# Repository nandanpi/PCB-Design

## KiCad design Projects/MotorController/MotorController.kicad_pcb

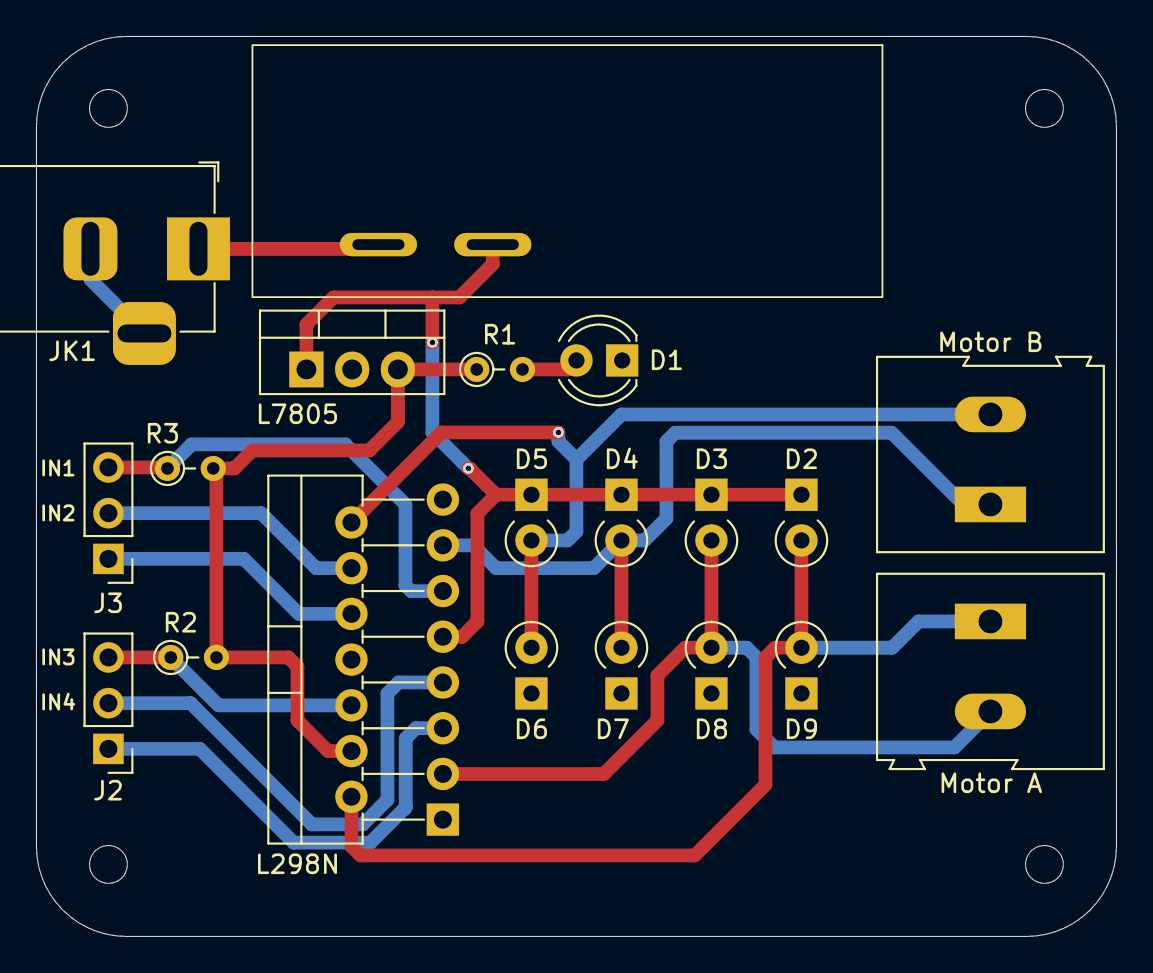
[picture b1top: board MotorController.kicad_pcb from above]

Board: 2 copper layers, 60.0 x 50.0 mm, 20 parts (0 on the bottom side), 15 nets.

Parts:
D1: LED; LED_D4.0mm
D2, D3, D4, D5, D6, D7, D8, D9: D; D_A-405_P2.54mm_Vertical_KathodeUp
J2, J3: Conn_01x03_Pin; PinHeader_1x03_P2.54mm_Vertical
JK1: BarrelJack_Horizontal
L298N: L298N; TO-220-15_P2.54x2.54mm_StaggerOdd_Lead4.58mm_Vertical
L7805: L7805; TO-220-3_Vertical
Motor A: Screw_Terminal_01x02; TerminalBlock_Altech_AK300-2_P5.00mm
Motor B: Screw_Terminal_01x02; TerminalBlock_Altech_AK300-2_P5.00mm
R1, R2, R3: R; R_Axial_DIN0204_L3.6mm_D1.6mm_P2.54mm_Vertical
SW1: SW_SPST; Slide_Switch_2pin

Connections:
+5V: L298N.4 (Vs), L7805.3 (OUT), R1.1, R2.2, R3.2
+12V: D2.1 (K), D3.1 (K), D4.1 (K), D5.1 (K), L298N.9 (Vss), L7805.1 (IN), SW1.2 (B)
GND: D1.1 (K), D6.1 (K), D7.1 (K), D8.1 (K), D9.1 (K), JK1.2 (GND), JK1.3 (MP), L298N.1 (SENSE_A), L298N.8 (GND), L298N.15 (SENSE_B), L7805.2 (GND)
unnamed: D1.2 (A), R1.2
unnamed: J2.1, L298N.5 (IN1)
unnamed: J2.2, L298N.7 (IN2)
unnamed: J2.3, L298N.6 (EnA), R2.1
unnamed: J3.1, L298N.10 (IN3)
unnamed: J3.2, L298N.12 (IN4)
unnamed: J3.3, L298N.11 (EnB), R3.1
unnamed: JK1.1 (IN), SW1.1 (A)
OUTA1: D2.2 (A), D9.2 (A), L298N.2 (OUT1), Motor A.1
OUTA2: D3.2 (A), D8.2 (A), L298N.3 (OUT2), Motor A.2
OUTB1: D4.2 (A), D7.2 (A), L298N.13 (OUT3), Motor B.1
OUTB2: D5.2 (A), D6.2 (A), L298N.14 (OUT4), Motor B.2

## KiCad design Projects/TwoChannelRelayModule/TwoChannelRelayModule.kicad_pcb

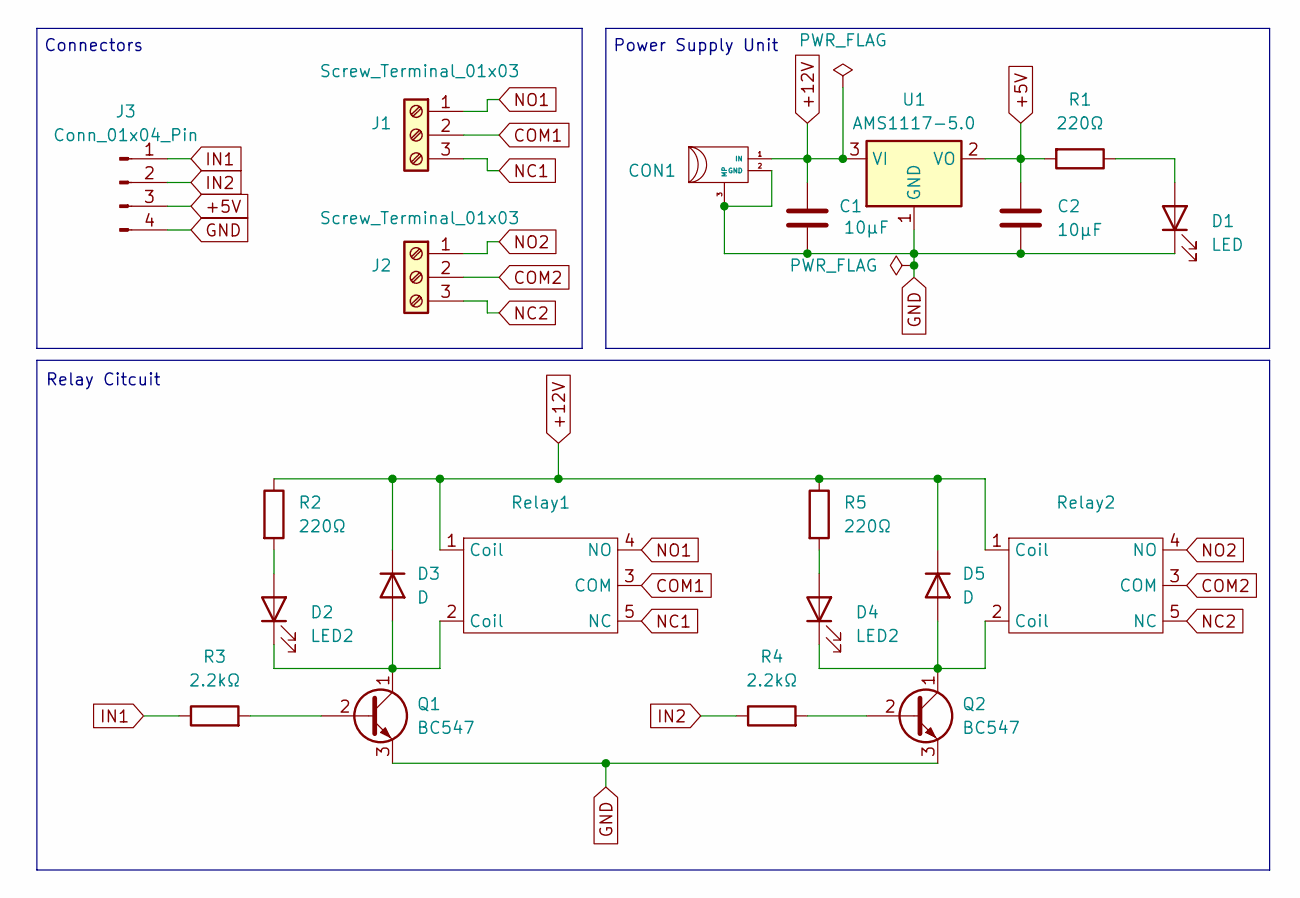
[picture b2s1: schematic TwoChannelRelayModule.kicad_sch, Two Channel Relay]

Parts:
C1, C2: 10µF; CP_Elec_4x5.8
CON1: BarrelJack_Horizontal
D1: LED; LED_0603_1608Metric
D2, D4: LED2; LED_0603_1608Metric
D3, D5: D; D_0603_1608Metric
J1, J2: Screw_Terminal_01x03; TerminalBlock_Altech_AK300-3_P5.00mm
J3: Conn_01x04_Pin; PinHeader_1x04_P2.54mm_Vertical
Q1, Q2: BC547; SOT-23
R1, R2, R5: 220Ω; R_0603_1608Metric
R3, R4: 2.2kΩ; R_0603_1608Metric
Relay1, Relay2: Relay
U1: AMS1117-5.0; SOT-223-3_TabPin2

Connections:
+5V: C2.1, J3.3, R1.2, U1.2 (VO)
+12V: C1.1, CON1.1 (IN), D3.1 (K), D5.1 (K), R2.1, R5.1, Relay1.1 (Coil), Relay2.1 (Coil), U1.3 (VI)
COM1: J1.2, Relay1.3 (COM)
COM2: J2.2, Relay2.3 (COM)
GND: C1.2, C2.2, CON1.2 (GND), CON1.3 (MP), D1.1 (K), J3.4, Q1.3 (E), Q2.3 (E), U1.1 (GND)
IN1: J3.1, R3.1
IN2: J3.2, R4.1
NC1: J1.3, Relay1.5 (NC)
NC2: J2.3, Relay2.5 (NC)
NO1: J1.1, Relay1.4 (NO)
NO2: J2.1, Relay2.4 (NO)
unnamed: D1.2 (A), R1.1
unnamed: D2.2 (A), R2.2
unnamed: D2.1 (K), D3.2 (A), Q1.1 (C), Relay1.2 (Coil)
unnamed: D4.2 (A), R5.2
unnamed: D4.1 (K), D5.2 (A), Q2.1 (C), Relay2.2 (Coil)
unnamed: Q1.2 (B), R3.2
unnamed: Q2.2 (B), R4.2

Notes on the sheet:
Relay Citcuit
Connectors
Power Supply Unit

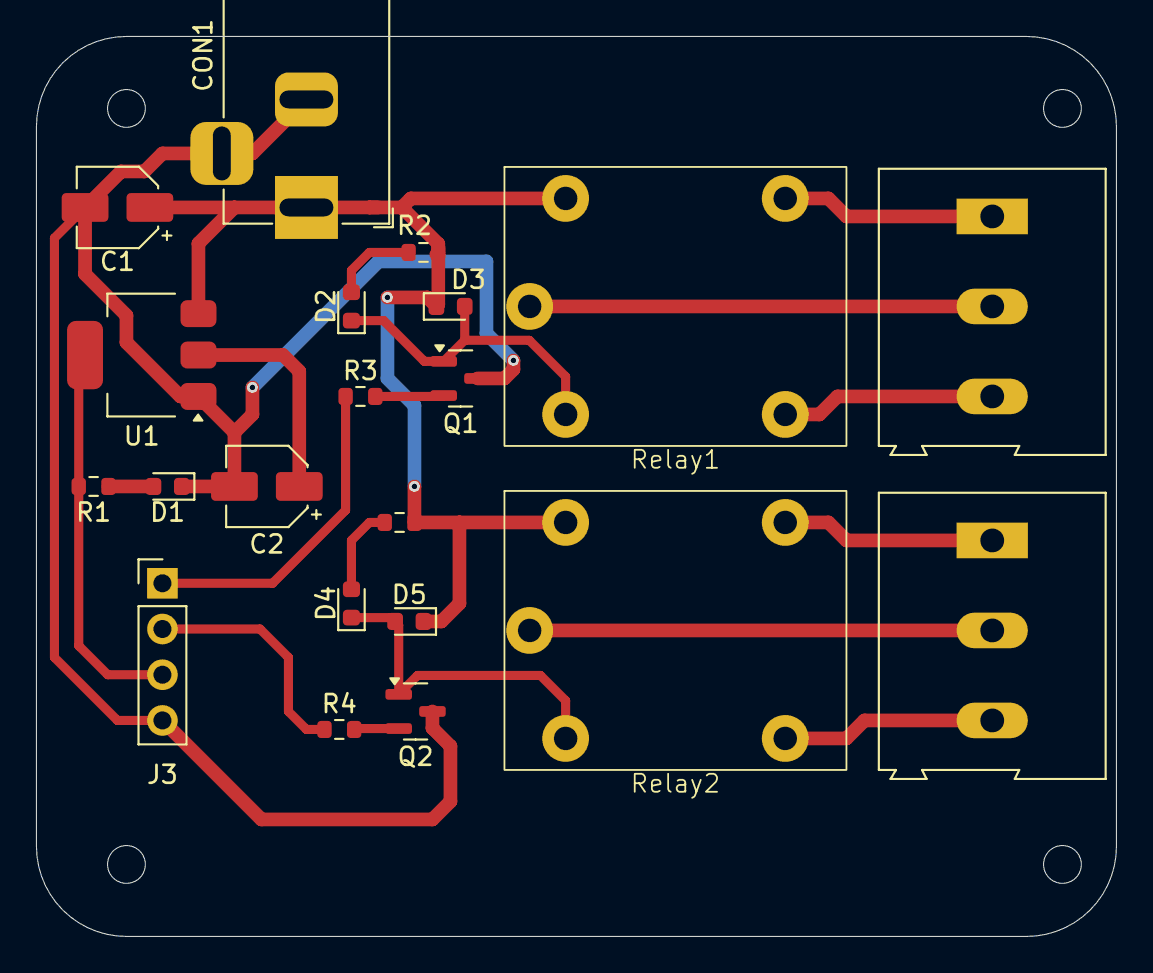
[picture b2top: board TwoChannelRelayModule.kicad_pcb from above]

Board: 2 copper layers, 60.0 x 50.0 mm, 21 parts (0 on the bottom side), 18 nets.

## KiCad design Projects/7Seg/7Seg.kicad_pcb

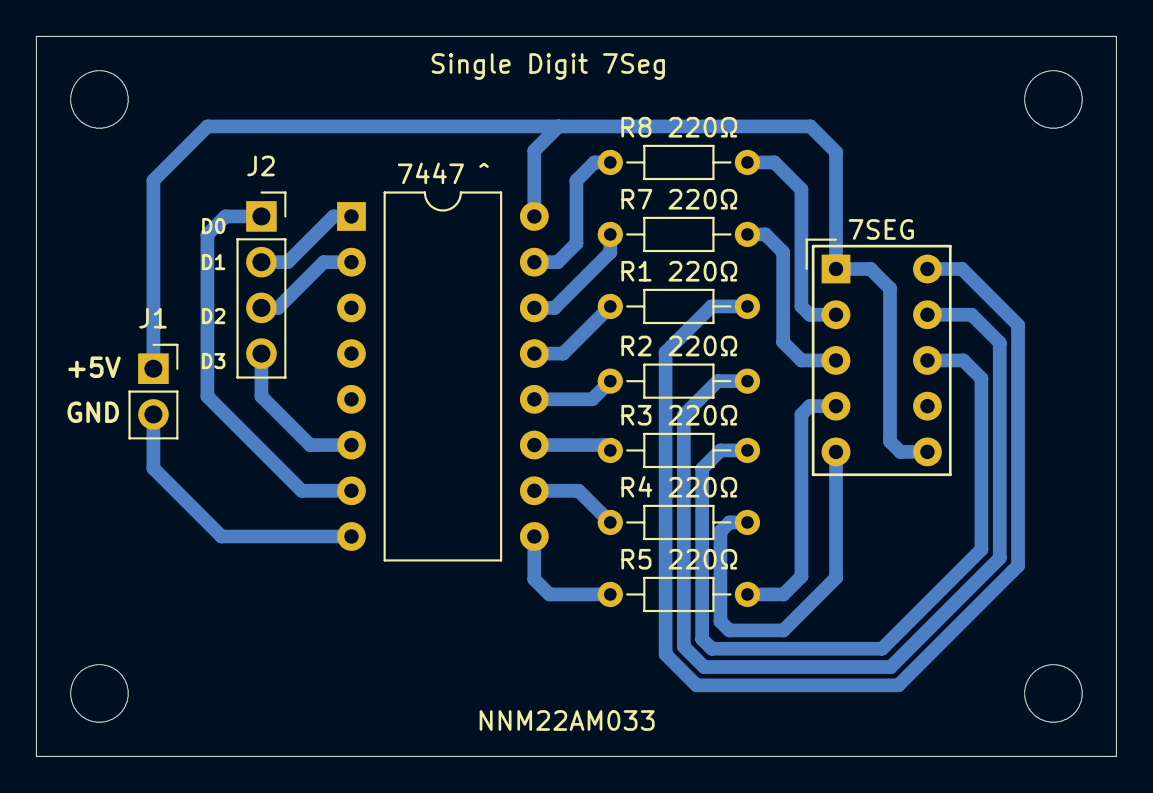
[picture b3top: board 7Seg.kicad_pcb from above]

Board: 2 copper layers, 60.0 x 40.0 mm, 11 parts (0 on the bottom side), 20 nets.

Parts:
7SEG: SA39-12EWA; HDSP-7401
7447 ^: 7447; DIP-16_W10.16mm
J1: Conn_01x02_Pin; PinSocket_1x02_P2.54mm_Vertical
J2: Conn_01x04_Pin; PinSocket_1x04_P2.54mm_Vertical
R1 220Ω, R2 220Ω, R3 220Ω, R4 220Ω, R5 220Ω, R7 220Ω, R8 220Ω: 220Ω; R_Axial_DIN0204_L3.6mm_D1.6mm_P7.62mm_Horizontal

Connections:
GND: 7447 ^.8 (GND), J1.2
unnamed: 7447 ^.7 (A), J2.1
unnamed: 7447 ^.1 (B), J2.2
unnamed: 7447 ^.2 (C), J2.3
unnamed: 7447 ^.6 (D), J2.4
unnamed: 7447 ^.13 (~a), R1 220Ω.1
unnamed: 7447 ^.12 (~b), R2 220Ω.1
unnamed: 7447 ^.11 (~c), R3 220Ω.1
unnamed: 7447 ^.10 (~d), R4 220Ω.1
unnamed: 7447 ^.9 (~e), R5 220Ω.1
unnamed: 7447 ^.15 (~f), R8 220Ω.1
unnamed: 7447 ^.14 (~g), R7 220Ω.1
unnamed: 7SEG.10 (A), R1 220Ω.2
unnamed: 7SEG.9 (B), R2 220Ω.2
unnamed: 7SEG.8 (C), R3 220Ω.2
unnamed: 7SEG.5 (D), R4 220Ω.2
unnamed: 7SEG.4 (E), R5 220Ω.2
unnamed: 7SEG.2 (F), R8 220Ω.2
unnamed: 7SEG.3 (G), R7 220Ω.2
VCC: 7SEG.1 (CA), 7SEG.6 (CA), 7447 ^.16 (VCC), J1.1

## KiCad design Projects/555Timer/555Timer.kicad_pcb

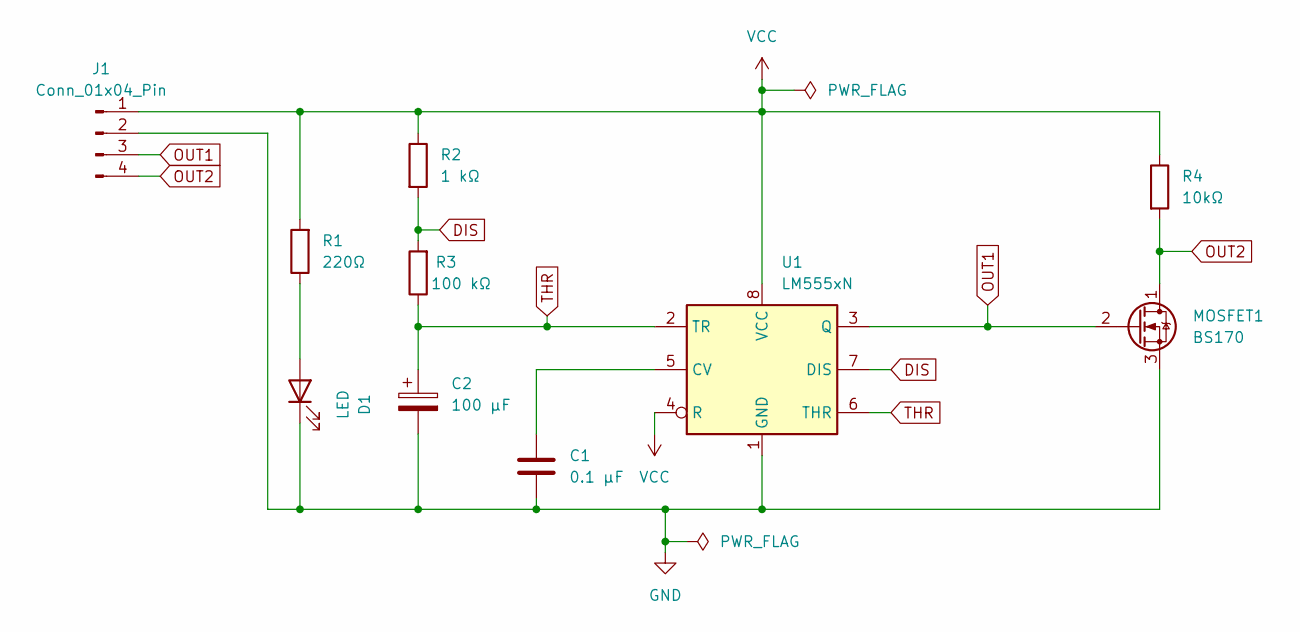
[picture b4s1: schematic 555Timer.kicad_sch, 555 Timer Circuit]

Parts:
C1: 0.1 µF; C_Disc_D5.0mm_W2.5mm_P5.00mm
C2: 100 µF; CP_Radial_Tantal_D5.0mm_P2.50mm
D1: LED; LED_D3.0mm
J1: Conn_01x04_Pin; PinSocket_1x04_P2.54mm_Vertical
MOSFET1: BS170; TO-92_Inline
R1: 220Ω; R_Axial_DIN0204_L3.6mm_D1.6mm_P7.62mm_Horizontal
R2: 1 kΩ; R_Axial_DIN0204_L3.6mm_D1.6mm_P7.62mm_Horizontal
R3: 100 kΩ; R_Axial_DIN0204_L3.6mm_D1.6mm_P7.62mm_Horizontal
R4: 10kΩ; R_Axial_DIN0204_L3.6mm_D1.6mm_P7.62mm_Horizontal
U1: LM555xN; DIP-8_W7.62mm

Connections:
DIS: R2.2, R3.2, U1.7 (DIS)
GND: C1.1, C2.2, D1.1 (K), J1.2, MOSFET1.3 (S), U1.1 (GND)
unnamed: D1.2 (A), R1.1
unnamed: C1.2, U1.5 (CV)
OUT1: J1.3, MOSFET1.2 (G), U1.3 (Q)
OUT2: J1.4, MOSFET1.1 (D), R4.2
THR: C2.1, R3.1, U1.2 (TR), U1.6 (THR)
VCC: J1.1, R1.2, R2.1, R4.1, U1.4 (R), U1.8 (VCC)

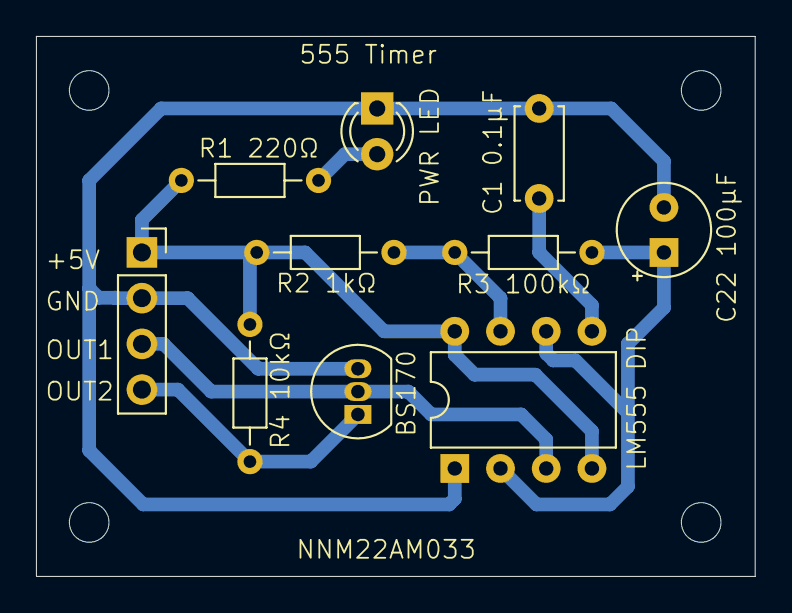
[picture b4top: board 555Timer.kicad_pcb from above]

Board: 2 copper layers, 39.9 x 30.0 mm, 10 parts (0 on the bottom side), 8 nets.

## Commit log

2025-01-15 555 Timer Schema
2025-01-15 refac: Folder structure
2025-01-22 555 Timer Layout
2025-02-11 Updte
2025-03-09 Motor Controller
